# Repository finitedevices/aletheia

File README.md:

# Aletheia
Designs and resources for the Finite Aletheia: a versatile, 8-bit hand-bootstrapped computer.

## Building and running the simulator
Before building the simulator for the first time, ensure that development dependencies are installed by running:

```bash
cd simulator
./build.sh --install-dev
```

Once the dependencies are installed, the Aletheia simulator can be built and run by running the following in the `simulator` directory:

```bash
./build.sh && python3 -m http.server
```

The simulator will then be available at [localhost:8000](http://localhost:8000).

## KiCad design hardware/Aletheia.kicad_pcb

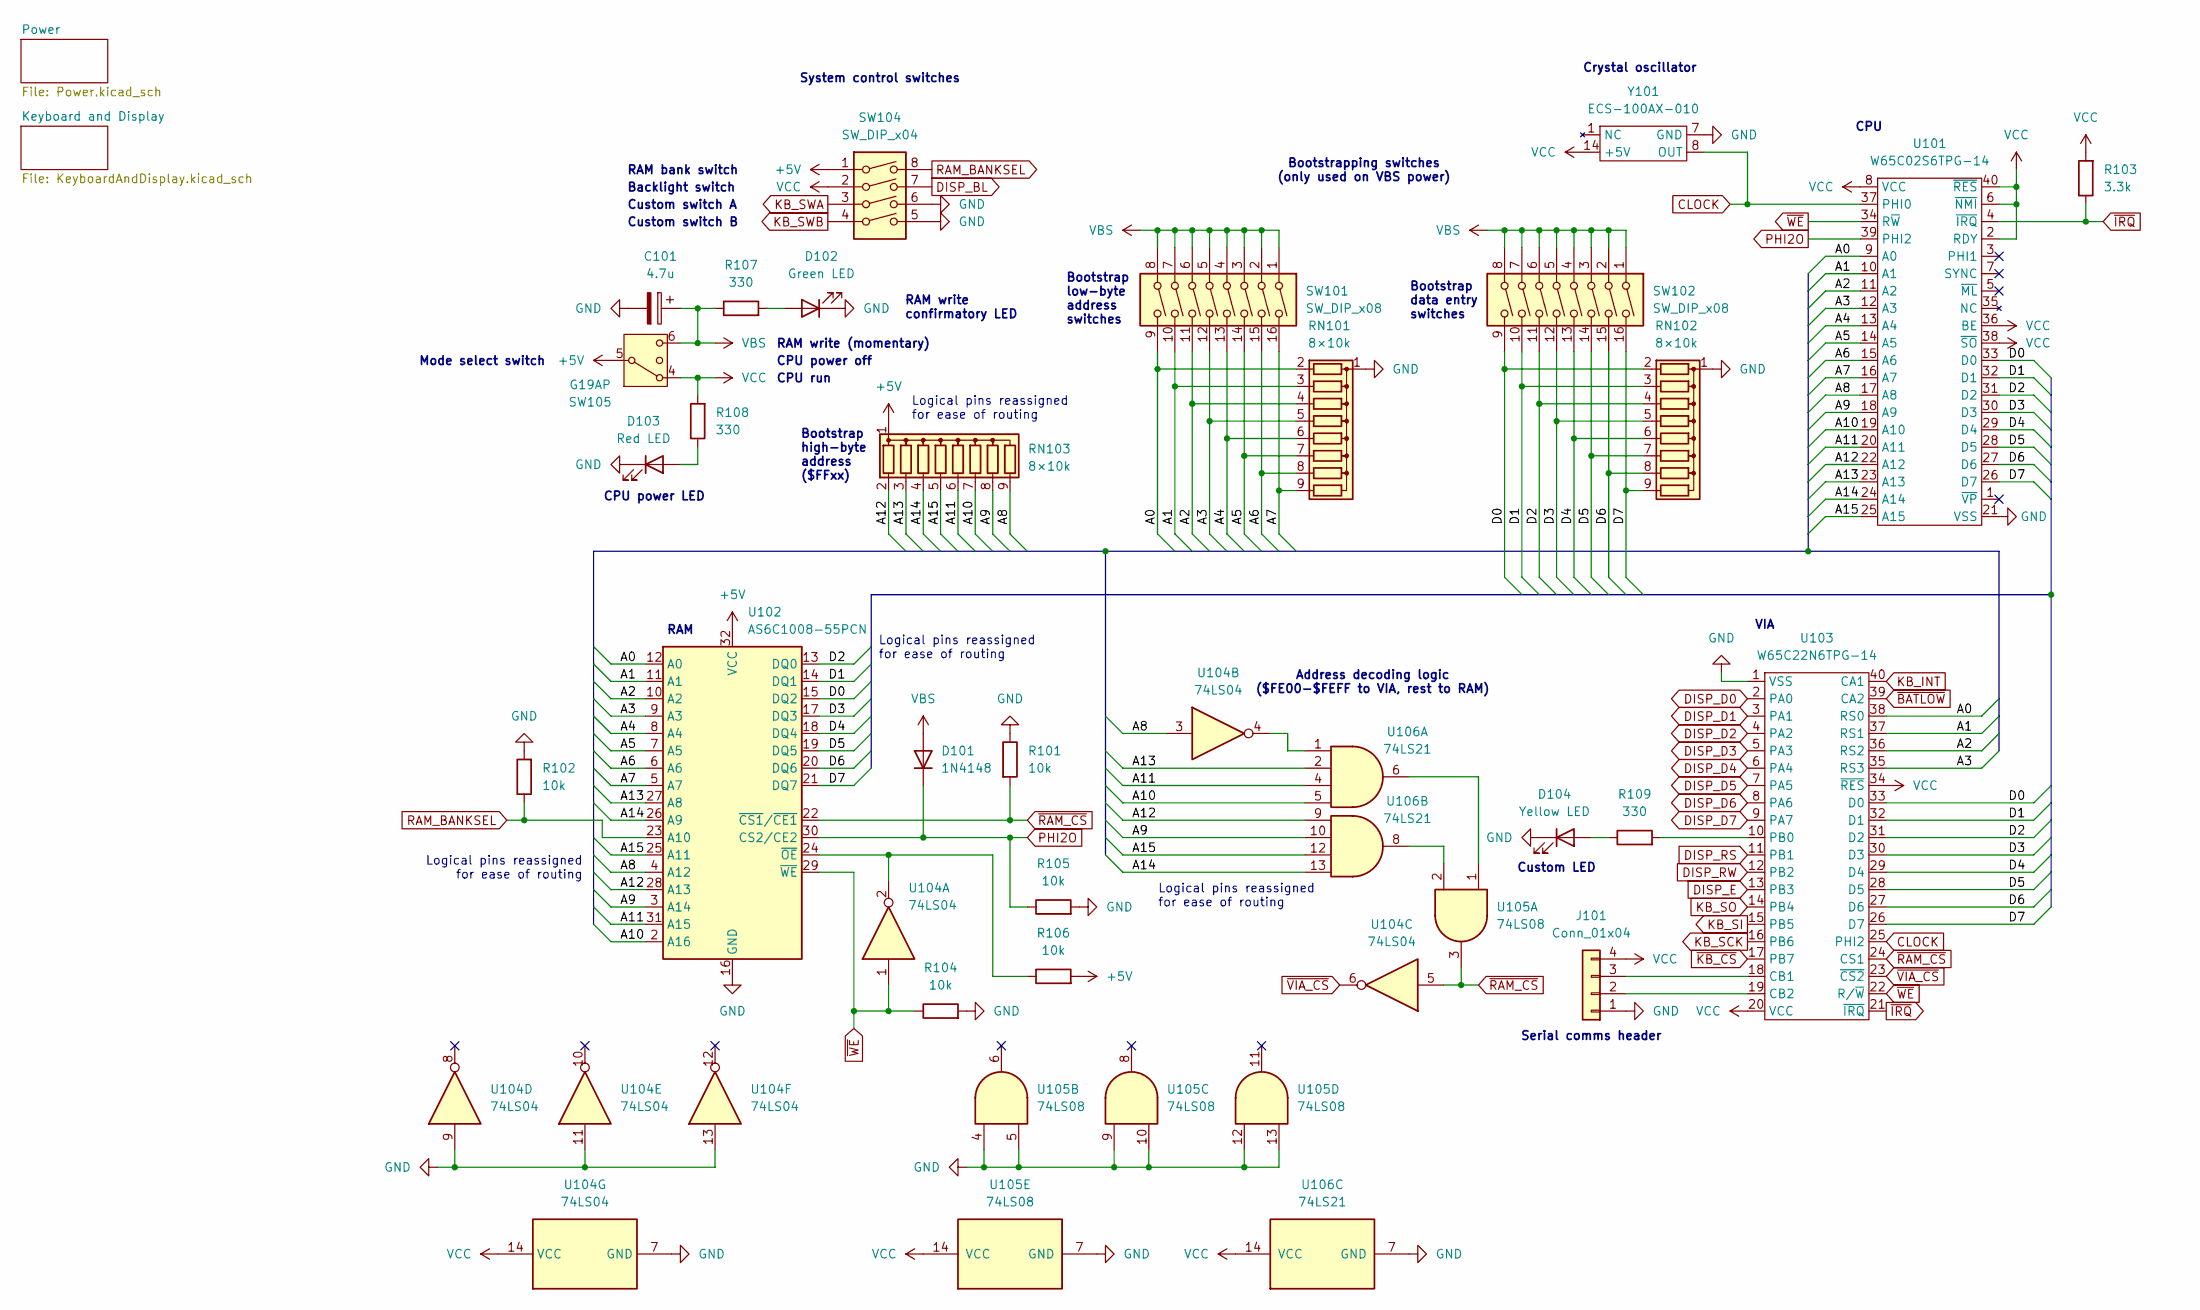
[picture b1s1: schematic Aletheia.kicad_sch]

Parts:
C101: 4.7u; CP_Radial_D5.0mm_P2.00mm
D101: 1N4148; D_DO-35_SOD27_P7.62mm_Horizontal
D102: Green LED; LED_D5.0mm
D103: Red LED; LED_D5.0mm
D104: Yellow LED; LED_D5.0mm
J101: Conn_01x04; PinHeader_1x04_P2.54mm_Vertical
R101, R102, R104, R105, R106: 10k; R_Axial_DIN0207_L6.3mm_D2.5mm_P7.62mm_Horizontal
R103: 3.3k; R_Axial_DIN0207_L6.3mm_D2.5mm_P7.62mm_Horizontal
R107, R108, R109: 330; R_Axial_DIN0207_L6.3mm_D2.5mm_P7.62mm_Horizontal
RN101, RN102, RN103: 8×10k; R_Array_SIP9
SW101, SW102: SW_DIP_x08; SW_DIP_SPSTx08_Slide_9.78x22.5mm_W7.62mm_P2.54mm
SW104: SW_DIP_x04; SW_DIP_SPSTx04_Slide_9.78x12.34mm_W7.62mm_P2.54mm
SW105: G19AP
U101: W65C02S6TPG-14; DIP-40_W15.24mm_LongPads
U102: AS6C1008-55PCN; DIP-32_W15.24mm
U103: W65C22N6TPG-14; DIP-40_W15.24mm
U104: 74LS04; DIP-14_W7.62mm
U105: 74LS08; DIP-14_W7.62mm
U106: 74LS21; DIP-14_W7.62mm
Y101: ECS-100AX-010

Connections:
+5V: R106.2, RN103.1 (common), SW104.1, SW105.5, U102.32 (VCC); also elsewhere on the board
/A0: RN101.2 (R1), SW101.9, U101.9 (A0), U102.12 (A0), U103.38 (RS0)
/A1: RN101.3 (R2), SW101.10, U101.10 (A1), U102.11 (A1), U103.37 (RS1)
/A2: RN101.4 (R3), SW101.11, U101.11 (A2), U102.10 (A2), U103.36 (RS2)
/A3: RN101.5 (R4), SW101.12, U101.12 (A3), U102.9 (A3), U103.35 (RS3)
/A4: RN101.6 (R5), SW101.13, U101.13 (A4), U102.8 (A4)
/A5: RN101.7 (R6), SW101.14, U101.14 (A5), U102.7 (A5)
/A6: RN101.8 (R7), SW101.15, U101.15 (A6), U102.6 (A6)
/A7: RN101.9 (R8), SW101.16, U101.16 (A7), U102.5 (A7)
/A8: RN103.9 (R8), U101.17 (A8), U102.4 (A12), U104.3
/A9: RN103.8 (R7), U101.18 (A9), U102.3 (A14), U106.10
/A10: RN103.7 (R6), U101.19 (A10), U102.2 (A16), U106.5
/A11: RN103.6 (R5), U101.20 (A11), U102.31 (A15), U106.4
/A12: RN103.2 (R1), U101.22 (A12), U102.28 (A13), U106.9
/A13: RN103.3 (R2), U101.23 (A13), U102.27 (A8), U106.2
/A14: RN103.4 (R3), U101.24 (A14), U102.26 (A9), U106.13
/A15: RN103.5 (R4), U101.25 (A15), U102.25 (A11), U106.12
/D0: RN102.2 (R1), SW102.9, U101.33 (D0), U102.15 (DQ2), U103.33 (D0)
/D1: RN102.3 (R2), SW102.10, U101.32 (D1), U102.14 (DQ1), U103.32 (D1)
/D2: RN102.4 (R3), SW102.11, U101.31 (D2), U102.13 (DQ0), U103.31 (D2)
/D3: RN102.5 (R4), SW102.12, U101.30 (D3), U102.17 (DQ3), U103.30 (D3)
/D4: RN102.6 (R5), SW102.13, U101.29 (D4), U102.18 (DQ4), U103.29 (D4)
/D5: RN102.7 (R6), SW102.14, U101.28 (D5), U102.19 (DQ5), U103.28 (D5)
/D6: RN102.8 (R7), SW102.15, U101.27 (D6), U102.20 (DQ6), U103.27 (D6)
/D7: RN102.9 (R8), SW102.16, U101.26 (D7), U102.21 (DQ7), U103.26 (D7)
CLOCK: U101.37 (PHI0), U103.25 (PHI2), Y101.8 (OUT)
DISP_BL: SW104.7; also elsewhere on the board
DISP_D0: U103.2 (PA0); also elsewhere on the board
DISP_D1: U103.3 (PA1); also elsewhere on the board
DISP_D2: U103.4 (PA2); also elsewhere on the board
DISP_D3: U103.5 (PA3); also elsewhere on the board
DISP_D4: U103.6 (PA4); also elsewhere on the board
DISP_D5: U103.7 (PA5); also elsewhere on the board
DISP_D6: U103.8 (PA6); also elsewhere on the board
DISP_D7: U103.9 (PA7); also elsewhere on the board
DISP_E: U103.13 (PB3); also elsewhere on the board
DISP_RS: U103.11 (PB1); also elsewhere on the board
DISP_RW: U103.12 (PB2); also elsewhere on the board
GND: C101.2, D102.1 (K), D103.1 (K), D104.1 (K), J101.1, R101.1, R102.2, R104.2, R105.2, RN101.1 (common), RN102.1 (common), SW104.5, SW104.6, U101.21 (VSS), U102.16 (GND), U103.1 (VSS), U104.7 (GND), U104.9, U104.11, U104.13, U105.4, U105.5, U105.7 (GND), U105.9, U105.10, U105.12, U105.13, U106.7 (GND), Y101.7 (GND); also elsewhere on the board
KB_INT: U103.40 (CA1); also elsewhere on the board
KB_SCK: U103.16 (PB6); also elsewhere on the board
KB_SI: U103.15 (PB5); also elsewhere on the board
KB_SO: U103.14 (PB4); also elsewhere on the board
KB_SWA: SW104.3; also elsewhere on the board
KB_SWB: SW104.4; also elsewhere on the board
unnamed: D102.2 (A), R107.2
unnamed: D103.2 (A), R108.1
unnamed: D104.2 (A), R109.1
unnamed: J101.2, U103.19 (CB2)
unnamed: J101.3, U103.18 (CB1)
unnamed: R106.1, U102.24 (~OE), U104.2
unnamed: R109.2, U103.10 (PB0)
unnamed: U104.4, U106.1
unnamed: U105.1, U106.6
unnamed: U105.2, U106.8
PHI2O: D101.1 (K), R105.1, U101.39 (PHI2), U102.30 (CS2/CE2)
RAM_BANKSEL: R102.1, SW104.8, U102.23 (A10)
VBS: C101.1, D101.2 (A), R107.1, SW101.1, SW101.2, SW101.3, SW101.4, SW101.5, SW101.6, SW101.7, SW101.8, SW102.1, SW102.2, SW102.3, SW102.4, SW102.5, SW102.6, SW102.7, SW102.8, SW105.6
VCC: J101.4, R103.2, R108.2, SW104.2, SW105.4, U101.2 (RDY), U101.6 (~NMI), U101.8 (VCC), U101.36 (BE), U101.38 (~SO), U101.40 (~RES), U103.20 (VCC), U103.34 (~RES), U104.14 (VCC), U105.14 (VCC), U106.14 (VCC), Y101.14 (+5V); also elsewhere on the board
~BATLOW: U103.39 (CA2); also elsewhere on the board
~IRQ: R103.1, U101.4 (~IRQ), U103.21 (~IRQ)
~KB_CS: U103.17 (PB7); also elsewhere on the board
~RAM_CS: R101.2, U102.22 (~CS1/~CE1), U103.24 (CS1), U104.5, U105.3
~VIA_CS: U103.23 (~CS2), U104.6
~WE: R104.1, U101.34 (R~W), U102.29 (~WE), U103.22 (R/~W), U104.1

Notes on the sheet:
Custom switch A
RAM
CPU
CPU run
Crystal oscillator
RAM write (momentary)
Bootstrap low-byte address switches
CPU power off
Bootstrap high-byte address ($FFxx)
Bootstrap data entry switches
Serial comms header
CPU power LED
Address decoding logic ($FE00-$FEFF to VIA, rest to RAM)
RAM write confirmatory LED
Bootstrapping switches (only used on VBS power)
Logical pins reassigned for ease of routing
VIA
Mode select switch
Backlight switch
RAM bank switch
Custom LED
System control switches
Custom switch B

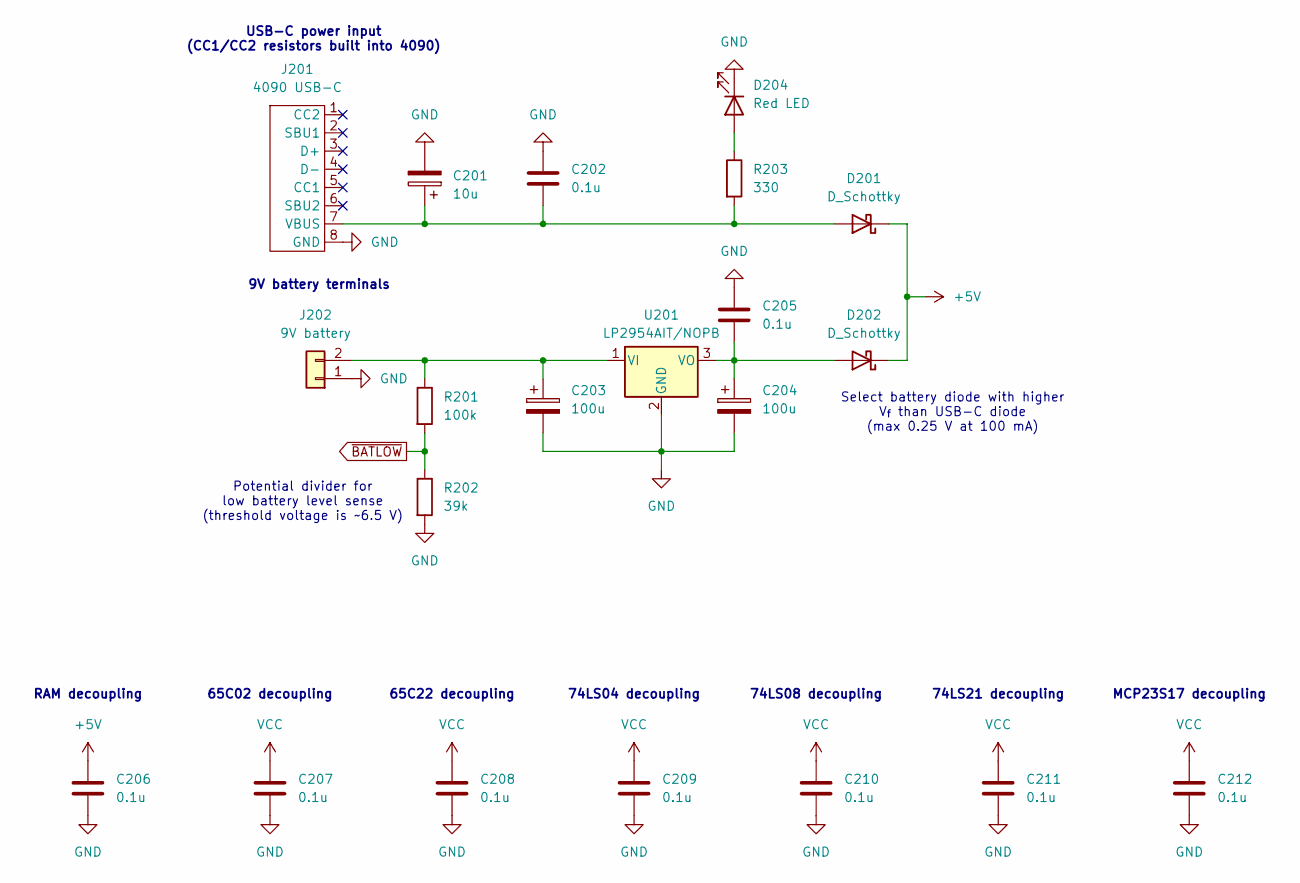
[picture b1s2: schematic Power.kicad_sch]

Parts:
C201: 10u; CP_Radial_D5.0mm_P2.00mm
C202: 0.1u; CP_Radial_D4.0mm_P1.50mm
C203, C204: 100u; CP_Radial_D6.3mm_P2.50mm
C205, C206, C207, C208, C209, C210, C211, C212: 0.1u; C_Radial_D4.0mm_H5.0mm_P1.50mm
D201, D202: D_Schottky; D_DO-41_SOD81_P7.62mm_Horizontal
D204: Red LED; LED_D5.0mm
J201: 4090 USB-C; PinHeader_1x08_P2.54mm_Vertical
J202: 9V battery; PinHeader_2x01_P2.54mm_Vertical
R201: 100k; R_Axial_DIN0207_L6.3mm_D2.5mm_P7.62mm_Horizontal
R202: 39k; R_Axial_DIN0207_L6.3mm_D2.5mm_P7.62mm_Horizontal
R203: 330; R_Axial_DIN0207_L6.3mm_D2.5mm_P7.62mm_Horizontal
U201: LP2954AIT/NOPB; TO-220-3_Vertical

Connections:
+5V: C206.1, D201.1 (K), D202.1 (K); also elsewhere on the board
GND: C201.2, C202.1, C203.2, C204.2, C205.1, C206.2, C207.2, C208.2, C209.2, C210.2, C211.2, C212.2, D204.1 (K), J201.8 (GND), J202.1, R202.2, U201.2 (GND); also elsewhere on the board
unnamed: C201.1, C202.2, D201.2 (A), J201.7 (VBUS), R203.2
unnamed: C204.1, C205.2, D202.2 (A), U201.3 (VO)
unnamed: D204.2 (A), R203.1
unnamed: C203.1, J202.2, R201.1, U201.1 (VI)
VCC: C207.1, C208.1, C209.1, C210.1, C211.1, C212.1; also elsewhere on the board
~BATLOW: R201.2, R202.1; also elsewhere on the board

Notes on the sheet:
RAM decoupling
74LS08 decoupling
MCP23S17 decoupling
Select battery diode with higher V_{f} than USB-C diode (max 0.25 V at 100 mA)
9V battery terminals
74LS04 decoupling
74LS21 decoupling
USB-C power input (CC1/CC2 resistors built into 4090)
65C02 decoupling
65C22 decoupling
Potential divider for low battery level sense (threshold voltage is ~6.5 V)

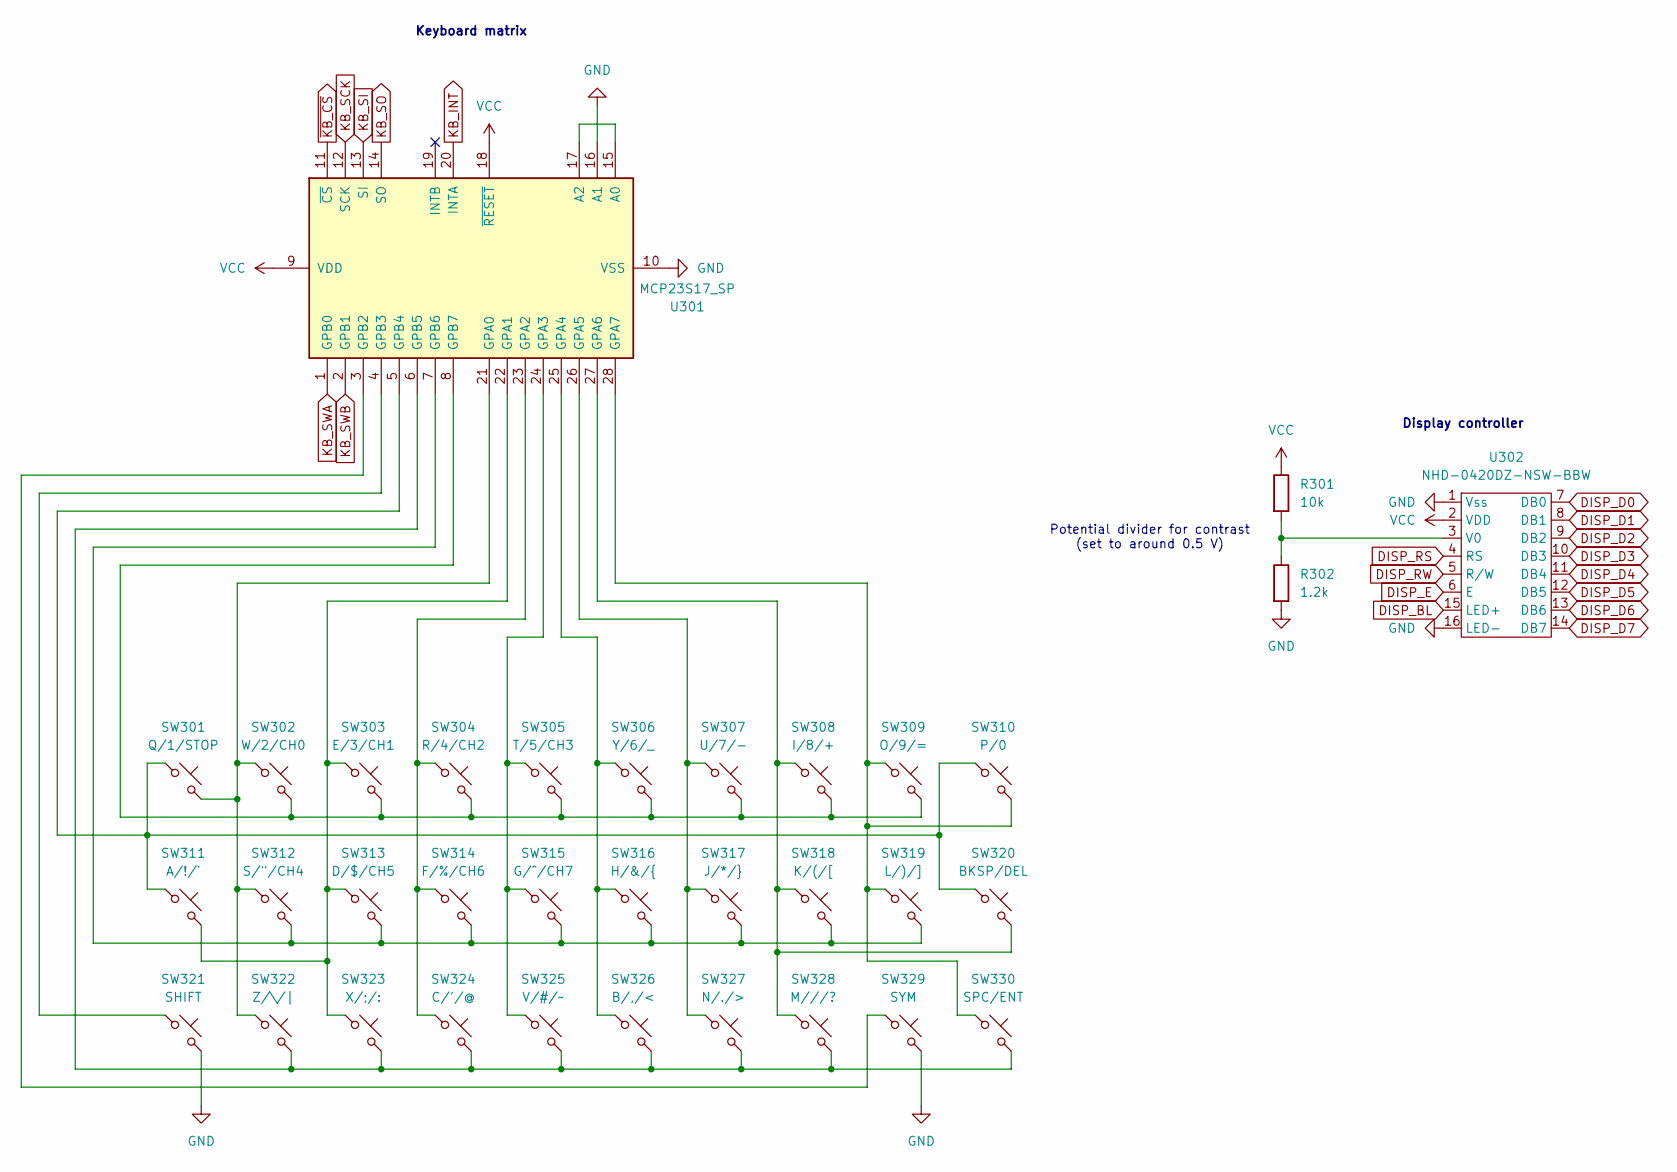
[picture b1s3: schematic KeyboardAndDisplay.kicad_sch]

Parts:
R301: 10k; R_Axial_DIN0207_L6.3mm_D2.5mm_P7.62mm_Horizontal
R302: 1.2k; R_Axial_DIN0207_L6.3mm_D2.5mm_P7.62mm_Horizontal
SW301: Q/1/STOP; SW_PUSH_6mm
SW302: W/2/CH0; SW_PUSH_6mm
SW303: E/3/CH1; SW_PUSH_6mm
SW304: R/4/CH2; SW_PUSH_6mm
SW305: T/5/CH3; SW_PUSH_6mm
SW306: Y/6/_; SW_PUSH_6mm
SW307: U/7/-; SW_PUSH_6mm
SW308: I/8/+; SW_PUSH_6mm
SW309: O/9/=; SW_PUSH_6mm
SW310: P/0; SW_PUSH_6mm
SW311: A/!/`; SW_PUSH_6mm
SW312: S/"/CH4; SW_PUSH_6mm
SW313: D/$/CH5; SW_PUSH_6mm
SW314: F/%/CH6; SW_PUSH_6mm
SW315: G/^/CH7; SW_PUSH_6mm
SW316: H/&/{; SW_PUSH_6mm
SW317: J/*/}; SW_PUSH_6mm
SW318: K/(/[; SW_PUSH_6mm
SW319: L/)/]; SW_PUSH_6mm
SW320: BKSP/DEL; SW_PUSH_6mm
SW321: SHIFT; SW_PUSH_6mm
SW322: Z/\/|; SW_PUSH_6mm
SW323: X/;/:; SW_PUSH_6mm
SW324: C/'/@; SW_PUSH_6mm
SW325: V/#/~; SW_PUSH_6mm
SW326: B/,/<; SW_PUSH_6mm
SW327: N/./>; SW_PUSH_6mm
SW328: M///?; SW_PUSH_6mm
SW329: SYM; SW_PUSH_6mm
SW330: SPC/ENT; SW_PUSH_6mm
U301: MCP23S17_SP; DIP-28_W7.62mm
U302: NHD-0420DZ-NSW-BBW; NHD-0420DZ-FL-YBW

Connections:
DISP_BL: U302.15 (LED+); also elsewhere on the board
DISP_D0: U302.7 (DB0); also elsewhere on the board
DISP_D1: U302.8 (DB1); also elsewhere on the board
DISP_D2: U302.9 (DB2); also elsewhere on the board
DISP_D3: U302.10 (DB3); also elsewhere on the board
DISP_D4: U302.11 (DB4); also elsewhere on the board
DISP_D5: U302.12 (DB5); also elsewhere on the board
DISP_D6: U302.13 (DB6); also elsewhere on the board
DISP_D7: U302.14 (DB7); also elsewhere on the board
DISP_E: U302.6 (E); also elsewhere on the board
DISP_RS: U302.4 (RS); also elsewhere on the board
DISP_RW: U302.5 (R/W); also elsewhere on the board
GND: R302.2, SW321.2, SW329.2, U301.10 (VSS), U301.16 (A1), U302.1 (Vss), U302.16 (LED-); also elsewhere on the board
KB_INT: U301.20 (INTA); also elsewhere on the board
KB_SCK: U301.12 (SCK); also elsewhere on the board
KB_SI: U301.13 (SI); also elsewhere on the board
KB_SO: U301.14 (SO); also elsewhere on the board
KB_SWA: U301.1 (GPB0); also elsewhere on the board
KB_SWB: U301.2 (GPB1); also elsewhere on the board
unnamed: U301.15 (A0), U301.17 (A2)
unnamed: SW301.2, SW302.1, SW312.1, SW322.1, U301.21 (GPA0)
unnamed: SW303.1, SW311.2, SW313.1, SW323.1, U301.22 (GPA1)
unnamed: SW304.1, SW314.1, SW324.1, U301.23 (GPA2)
unnamed: SW305.1, SW315.1, SW325.1, U301.24 (GPA3)
unnamed: SW306.1, SW316.1, SW326.1, U301.25 (GPA4)
unnamed: SW307.1, SW317.1, SW327.1, U301.26 (GPA5)
unnamed: SW308.1, SW318.1, SW320.2, SW328.1, U301.27 (GPA6)
unnamed: SW309.1, SW310.2, SW319.1, SW330.1, U301.28 (GPA7)
unnamed: SW329.1, U301.3 (GPB2)
unnamed: SW321.1, U301.4 (GPB3)
unnamed: SW301.1, SW310.1, SW311.1, SW320.1, U301.5 (GPB4)
unnamed: SW322.2, SW323.2, SW324.2, SW325.2, SW326.2, SW327.2, SW328.2, SW330.2, U301.6 (GPB5)
unnamed: SW312.2, SW313.2, SW314.2, SW315.2, SW316.2, SW317.2, SW318.2, SW319.2, U301.7 (GPB6)
unnamed: SW302.2, SW303.2, SW304.2, SW305.2, SW306.2, SW307.2, SW308.2, SW309.2, U301.8 (GPB7)
unnamed: R301.2, R302.1, U302.3 (V0)
VCC: R301.1, U301.9 (VDD), U301.18 (~RESET), U302.2 (VDD); also elsewhere on the board
~KB_CS: U301.11 (~CS); also elsewhere on the board

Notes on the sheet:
Display controller
Keyboard matrix
Potential divider for contrast (set to around 0.5 V)

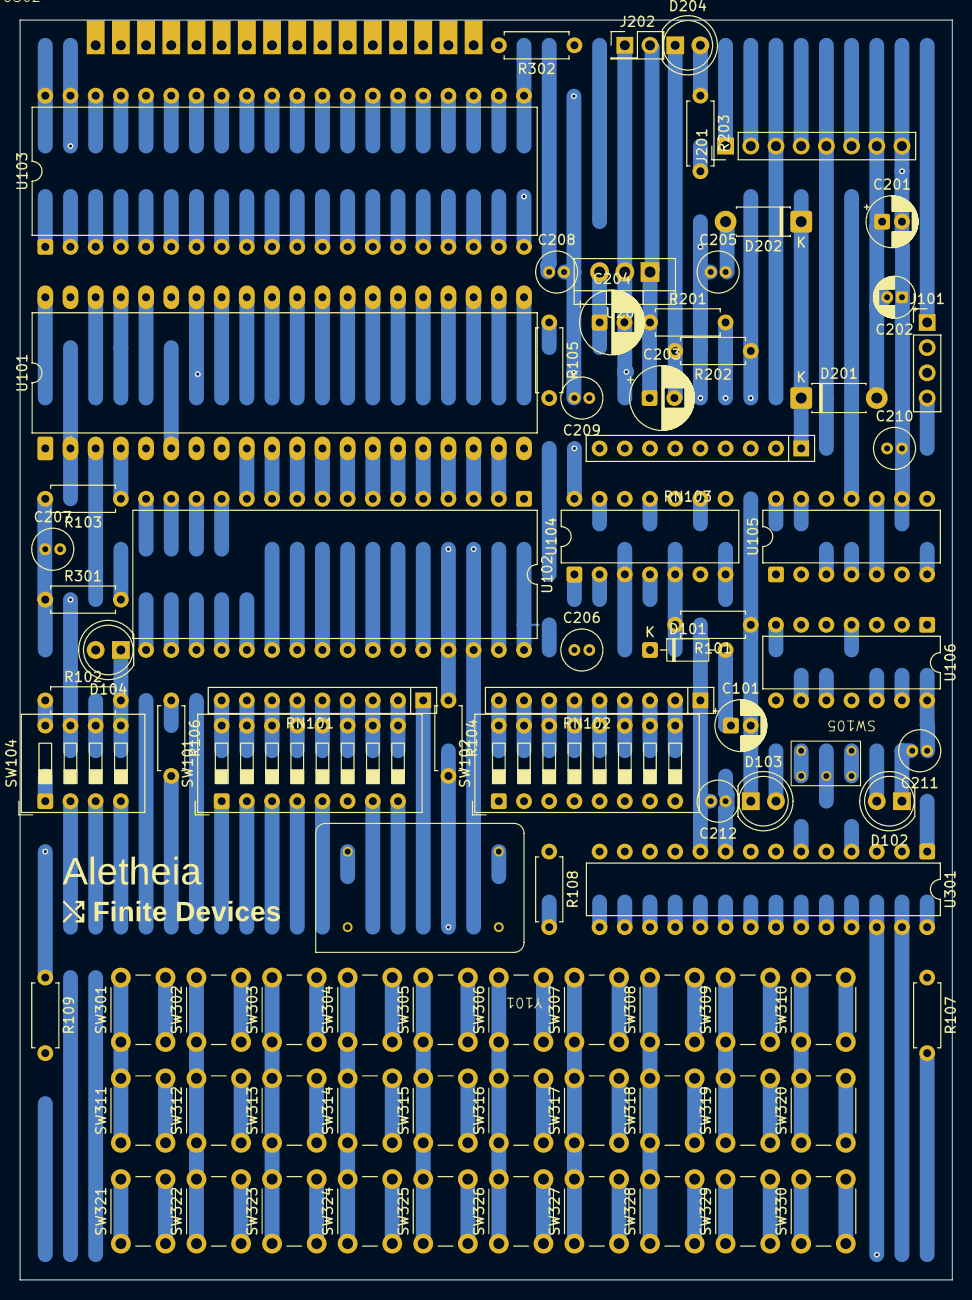
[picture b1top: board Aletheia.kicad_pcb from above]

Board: 12 copper layers, 94.0 x 127.0 mm, 84 parts (0 on the bottom side), 85 nets.

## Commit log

2026-01-13 Add final planned components
2026-01-14 Finish rough component wiring layout
2026-01-15 Modify power circuitry to use better diode arrangement and more energy-efficient regulator
2026-01-16 Add basic web simulator
2026-01-17 Fix badge branding
2026-01-19 Add basic simulator UI layout
2026-01-20 Add cutout version of badge
2026-01-20 Add back cutout
2026-01-20 Update back cutout export filename
2026-01-21 Fix footprint for crystal
2026-01-22 Allow setting offset when using code loader
2026-01-25 Fix wiring of crystal oscillator
2026-01-27 Add instructions for running the simulator
2026-01-31 Add small clarification to simulator in readme
2026-02-01 Add start of operator's manual
2026-02-01 Update operator's manual layout and compliance info
2026-02-01 Add basic 3D visualisation code
2026-02-02 Add getting started section to manual and add more details to 3D visualisation
2026-02-05 Fix asynchronous loading of WASM file in simulator
2026-02-06 Add DIP switches to 3D visualisation
2026-02-07 Fix missing trace wire in hardware
2026-02-08 Fix orientation of pins for mode switch in hardware
2026-04-28 Add minor clarification to readme
